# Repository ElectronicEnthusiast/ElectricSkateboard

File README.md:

# MotorController
Inverter Motor Control Board For BLDC Motor - 100V,100A

The motor controller board is generic, so it will comply with all Texas Instruments Launchpads using their "Boosterpack pin layout".
The board software utilizes a high performance F28379D Launchpad microcontroller development board from Texas Instruments.
The motor controller uses Texas Instruments integrated circuits to isolate the logic from the power components.

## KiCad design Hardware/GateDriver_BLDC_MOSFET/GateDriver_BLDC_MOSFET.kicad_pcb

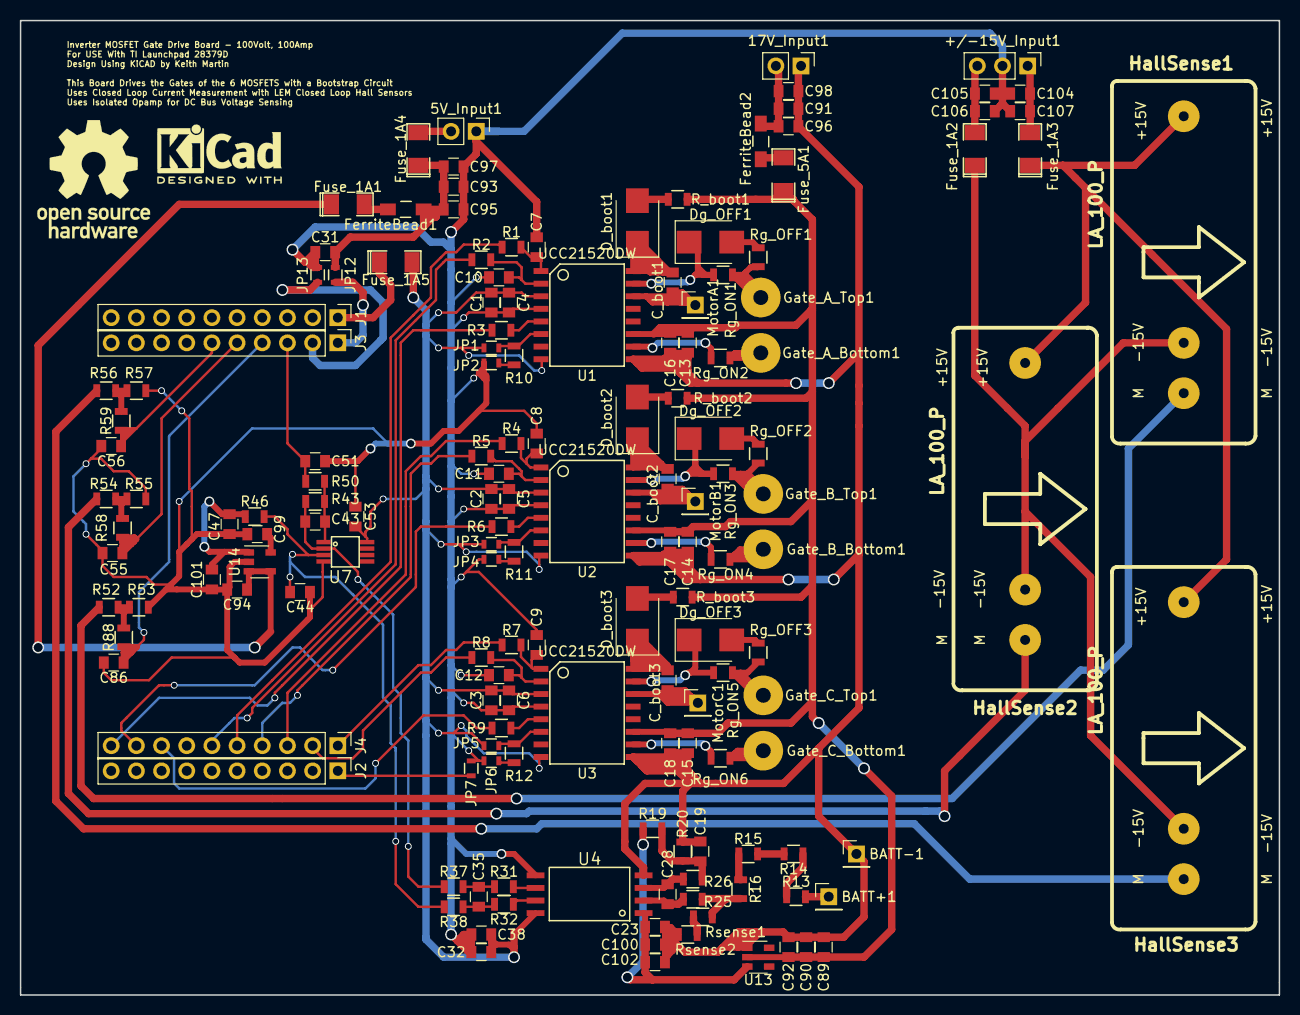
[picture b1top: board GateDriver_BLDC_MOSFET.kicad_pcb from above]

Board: 2 copper layers, 127.0 x 98.3 mm, 155 parts (0 on the bottom side), 95 nets.

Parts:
5V_Input1, 17V_Input1: CONN_01X02; Socket_Strip_Straight_1x02_Pitch2.54mm
+/-15V_Input1: CONN_01X03; Socket_Strip_Straight_1x03_Pitch2.54mm
BATT+1: BATT+; Socket_Strip_Straight_1x01_Pitch2.54mm
BATT-1: BATT-; Socket_Strip_Straight_1x01_Pitch2.54mm
C1, C2, C3, C13, C14, C15, C89, C90, C95, C96, C100, C106, C107: 10uF_ceramic; C_0805
C4, C5, C6, C16, C17, C18, C23, C38, C51, C92, C94, C97, C98, C99, C101, C102, C104, C105: 0.1uF_ceramic; C_0805
C7, C8, C9, C10, C11, C12: 10pF_ceramic; C_0805
C19, C28, C31, C35, C44, C47, C53: 0.01uF_ceramic; C_0805
C32, C91, C93: 4.7uF_ceramic; C_0805
C43: 180pF_ceramic; C_0805
C55, C56, C86: 1500pF_ceramic; C_0805
C_boot1, C_boot2, C_boot3: 0.47uF_ceramic; C_0805
D_boot1, D_boot2, D_boot3: VS-MBRS130L-M3; D_SMB_Standard
Dg_OFF1, Dg_OFF2, Dg_OFF3: VS-MBRS130L-M3; D_SMB_Standard
FerriteBead1, FerriteBead2: BLM31SN500SH1L; Choke_SMD_1206_Standard
Fuse_1A1, Fuse_1A2, Fuse_1A3, Fuse_1A4, Fuse_1A5: MFU1206FF01000P100; SMD-1206_Pol
Fuse_5A1: MFU1206FF05000P100; SMD-1206_Pol
Gate_A_Bottom1: Gate_A_Bottom; SolderWirePad_single_1-5mmDrill
Gate_A_Top1: Gate_A_Top; SolderWirePad_single_1-5mmDrill
Gate_B_Bottom1: Gate_B_Bottom; SolderWirePad_single_1-5mmDrill
Gate_B_Top1: Gate_B_Top; SolderWirePad_single_1-5mmDrill
Gate_C_Bottom1: Gate_C_Bottom; SolderWirePad_single_1-5mmDrill
Gate_C_Top1: Gate_C_Top; SolderWirePad_single_1-5mmDrill
HallSense1, HallSense2, HallSense3: LA_100_P; la_55_p
J1: TI_BOOSTER_40_J1; Socket_Strip_Straight_1x10_Pitch2.54mm
J2: TI_BOOSTER_40_J2; Socket_Strip_Straight_1x10_Pitch2.54mm
J3: TI_BOOSTER_40_J3; Socket_Strip_Straight_1x10_Pitch2.54mm
J4: TI_BOOSTER_40_J4; Socket_Strip_Straight_1x10_Pitch2.54mm
JP1, JP3, JP5, JP7, JP12, JP13: Jumper_NC_Small; R_0603
JP2, JP4, JP6: Jumper_NO_Small; R_0603
MotorA1: MotorA; Socket_Strip_Straight_1x01_Pitch2.54mm
MotorB1: MotorB; Socket_Strip_Straight_1x01_Pitch2.54mm
MotorC1: MotorC; Socket_Strip_Straight_1x01_Pitch2.54mm
R1, R2, R3, R4, R5, R6, R7, R8, R9: 10; R_0805
R10, R11, R12: 1k; R_0805
R13, R14, R15, R16: KTR10EZPF1004; R_0805
R19: 50k; R_0805
R20: 4.1k; R_0805
R25, R26: 39; R_0805
R31, R32, R37, R38, R46: 4.7k; R_0805
R43: 7.5k; R_0805
R50, R58, R59, R88: 100; R_0805
R52, R54, R56: 17.16; R_0805
R53, R55, R57: 4.84; R_0805
R_boot1, R_boot2, R_boot3: 2.2; R_0805
Rg_OFF1, Rg_OFF2, Rg_OFF3: 0; R_0805
Rg_ON1, Rg_ON2, Rg_ON3, Rg_ON4, Rg_ON5, Rg_ON6: 10; R_0805
Rsense1: 101; R_0805
Rsense2: 20k; R_0805
U1, U2, U3: UCC21520DW; SOIC-16W_7.5x10.3mm_Pitch1.27mm
U4: AMC1301DWVR; SOIC-8-DWV
U7: OPA2320AIDGKR; VSSOP-8
U13: TLV70433DBVR; SOT-23-5
U14: REF2033AIDDCR; SOT-23-5

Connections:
+3V3: C1.1, C2.1, C3.1, C4.1, C5.1, C6.1, C32.1, C38.1, C53.1, Fuse_1A5.2, JP1.1, JP3.1, JP5.1, U1.3, U1.8, U2.3, U2.8, U3.3, U3.8, U4.8, U7.8
+5V: C31.1, C93.1, C95.1, C97.1, FerriteBead1.2, Fuse_1A4.1, JP12.1
+15V: Fuse_1A3.1, HallSense1.1, HallSense2.1, HallSense3.1
+BATT: BATT+1.1, R13.2
-15V: Fuse_1A2.1, HallSense1.2, HallSense2.2, HallSense3.2
BatteryBusVoltage: C51.1, J3.3, R50.1
BusVoltageIn+: C44.1, R38.1, R46.2, U7.3
BusVoltageIn-: C43.2, R37.1, R43.1, U7.2
BusVoltageOpampOutput: C43.1, R43.2, R50.2, U7.1
GND: 5V_Input1.1, +/-15V_Input1.2, C1.2, C2.2, C3.2, C4.2, C5.2, C6.2, C7.2, C8.2, C9.2, C10.2, C11.2, C12.2, C31.2, C32.2, C38.2, C44.2, C47.2, C51.2, C53.2, C55.2, C56.2, C86.2, C93.2, C94.2, C95.2, C97.2, C99.2, C101.2, C104.2, C105.1, C106.1, C107.2, JP2.1, JP4.1, JP6.1, JP7.2, JP13.1, R53.2, R55.2, R57.2, U1.4, U2.4, U3.4, U4.5, U7.4, U14.2
Isol_+3.3V: C23.1, C100.1, C102.1, R19.1, U4.1, U13.3
unnamed: 5V_Input1.2, Fuse_1A4.2
unnamed: 17V_Input1.2, C91.1, C96.1, C98.1, FerriteBead2.2
unnamed: +/-15V_Input1.1, C104.1, C107.1, Fuse_1A3.2
unnamed: +/-15V_Input1.3, C105.2, C106.2, Fuse_1A2.2
unnamed: C7.1, R1.1, U1.1
unnamed: C8.1, R4.1, U2.1
unnamed: C9.1, R7.1, U3.1
unnamed: C10.1, R2.1, U1.2
unnamed: C11.1, R5.1, U2.2
unnamed: C12.1, R8.1, U3.2
unnamed: C19.1, R19.2, R20.1, R26.2
unnamed: C28.1, R25.1, U4.2
unnamed: C28.2, R26.1, U4.3
unnamed: C35.1, R31.1, R37.2
unnamed: C35.2, R32.1, R38.2
unnamed: C94.1, Fuse_1A1.1, U14.3, U14.4
unnamed: C99.1, U14.5
unnamed: C_boot1.1, D_boot1.1, U1.16
unnamed: C_boot1.2, MotorA1.1, U1.14
unnamed: C_boot2.1, D_boot2.1, U2.16
unnamed: C_boot2.2, MotorB1.1, U2.14
unnamed: C_boot3.1, D_boot3.1, U3.16
unnamed: C_boot3.2, MotorC1.1, U3.14
unnamed: D_boot1.2, R_boot1.1
unnamed: D_boot2.2, R_boot2.1
unnamed: D_boot3.2, R_boot3.1
unnamed: Dg_OFF1.1, Rg_ON1.2, U1.15
unnamed: Dg_OFF1.2, Rg_OFF1.2
unnamed: Dg_OFF2.1, Rg_ON3.2, U2.15
unnamed: Dg_OFF2.2, Rg_OFF2.2
unnamed: Dg_OFF3.1, Rg_ON5.2, U3.15
unnamed: Dg_OFF3.2, Rg_OFF3.2
unnamed: FerriteBead1.1, Fuse_1A1.2
unnamed: FerriteBead2.1, Fuse_5A1.2
unnamed: Fuse_1A5.1, J1.1
unnamed: Gate_A_Bottom1.1, Rg_ON2.1
unnamed: Gate_A_Top1.1, Rg_OFF1.1, Rg_ON1.1
unnamed: Gate_B_Bottom1.1, Rg_ON4.1
unnamed: Gate_B_Top1.1, Rg_OFF2.1, Rg_ON3.1
unnamed: Gate_C_Bottom1.1, Rg_ON6.1
unnamed: Gate_C_Top1.1, Rg_OFF3.1, Rg_ON5.1
unnamed: HallSense1.3, R52.1
unnamed: HallSense2.3, R54.1
unnamed: HallSense3.3, R56.1
unnamed: J2.1, JP7.1
unnamed: J3.1, JP12.2
unnamed: J3.2, JP13.2
unnamed: J4.1, R7.2
unnamed: J4.2, R8.2
unnamed: J4.3, R4.2
unnamed: J4.4, R5.2
unnamed: J4.5, R1.2
unnamed: J4.6, R2.2
unnamed: J4.8, R9.2
unnamed: J4.9, R6.2
unnamed: J4.10, R3.2
unnamed: JP1.2, R10.1, U1.6
unnamed: JP2.2, R10.2
unnamed: JP3.2, R11.1, U2.6
unnamed: JP4.2, R11.2
unnamed: JP5.2, R12.1, U3.6
unnamed: JP6.2, R12.2
unnamed: R3.1, U1.5
unnamed: R6.1, U2.5
unnamed: R9.1, U3.5
unnamed: R13.1, R14.2
unnamed: R14.1, R15.2
unnamed: R15.1, R16.2
unnamed: R16.1, R25.2, Rsense1.2
unnamed: R31.2, U4.6
unnamed: R32.2, U4.7
unnamed: R52.2, R53.1, R88.2
unnamed: R54.2, R55.1, R58.2
unnamed: R56.2, R57.1, R59.2
unnamed: Rg_ON2.2, U1.10
unnamed: Rg_ON4.2, U2.10
unnamed: Rg_ON6.2, U3.10
unnamed: Rsense1.1, Rsense2.2
PhaseA_Current: C86.1, J3.4, R88.1
PhaseB_Current: C55.1, J3.5, R58.1
PhaseC_Current: C56.1, J3.6, R59.1
VDD: C13.1, C14.1, C15.1, C16.1, C17.1, C18.1, C89.1, C90.1, C92.1, Fuse_5A1.1, R_boot1.2, R_boot2.2, R_boot3.2, U1.11, U2.11, U3.11, U13.2
VEE: C47.1, C101.1, R46.1, U14.1
VSS: 17V_Input1.1, BATT-1.1, C13.2, C14.2, C15.2, C16.2, C17.2, C18.2, C19.2, C23.2, C89.2, C90.2, C91.2, C92.2, C96.2, C98.2, C100.2, C102.2, R20.2, Rsense2.1, U1.9, U2.9, U3.9, U4.4, U13.1

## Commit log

2017-05-28 :boom::camel: Added .gitattributes & .gitignore files
2017-05-28 FirstCommit
2017-05-28 Added hardware files from old repository
    now I can upload updates from TI's CCS program and still have the
    hardware in the same repository
2017-05-28 test
2017-05-28 Added More Pictures and Fixed Linking to CCS
2017-07-04 Phase2 Working Software_LEM Current Sense on Pins B4&C4
    LEM Current Sensing on Pins B4&C4
    Changed Max Current to 25A (100/4turns through LEM)
2017-07-04 Fixed Frequency Change To Normal & Added Pictures
2017-07-21 Diagnosing GateDriverBoard
    2/3 Gate Drives working.
    U3 is not working right.
